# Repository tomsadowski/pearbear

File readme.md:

# Pearbear

2) Order the PCB
  * 1) Download the [specification file](mx/production/pearbear_mx.zip)
  * 2) Upload the file to a PCB [fabrication service](https://jlcpcb.com/)
3) Bill of Materials
  * a) 2x [Adafruit KB2040](https://www.adafruit.com/product/5302#tutorials)
    * product id: 5302
    * [datasheet](datasheets/Adafruit_KB2040_Pinout.pdf)
  * b) 2x [6P6C RJ11 socket](https://www.digikey.com/en/products/detail/w%C3%BCrth-elektronik/615006138421/2060609) 
    * manufacturer product number: 615006138421
    * digikey part number: 732-2113-ND
    * [datasheet](datasheets/WR-MJ.pdf)
  * c) 2x [6mm B3F-10xx tactile switches](https://www.digikey.com/en/products/detail/adafruit-industries-llc/367/10669771)
    * manufacturer product number: 367
    * digikey part number: 1528-367-ND
    * [datasheet](datasheets/B3F-1000-Omron.pdf)
  * d) 34x [Cherry MX switches](https://mechanicalkeyboards.com/products/cherry-mx2a-silent-red-45g-linear)
    * [datasheet](datasheets/Cherry_MX.pdf)
  * e) 34x [XDA Keycaps](https://ymdkey.com/products/xda-1u-new-keycapsblank-pbt-1-55mm)
  * f) Substrate
    * 1x Mousepad
    * gorilla glue
4) Assembly
  * 1) Solder 3.a - 3.d to PCB (beginners guide pending)
  * 2) Cut the mousepad into strips and glue the strips along the bottom of the PCB
5) Flash microcontrollers with qmk_firmware

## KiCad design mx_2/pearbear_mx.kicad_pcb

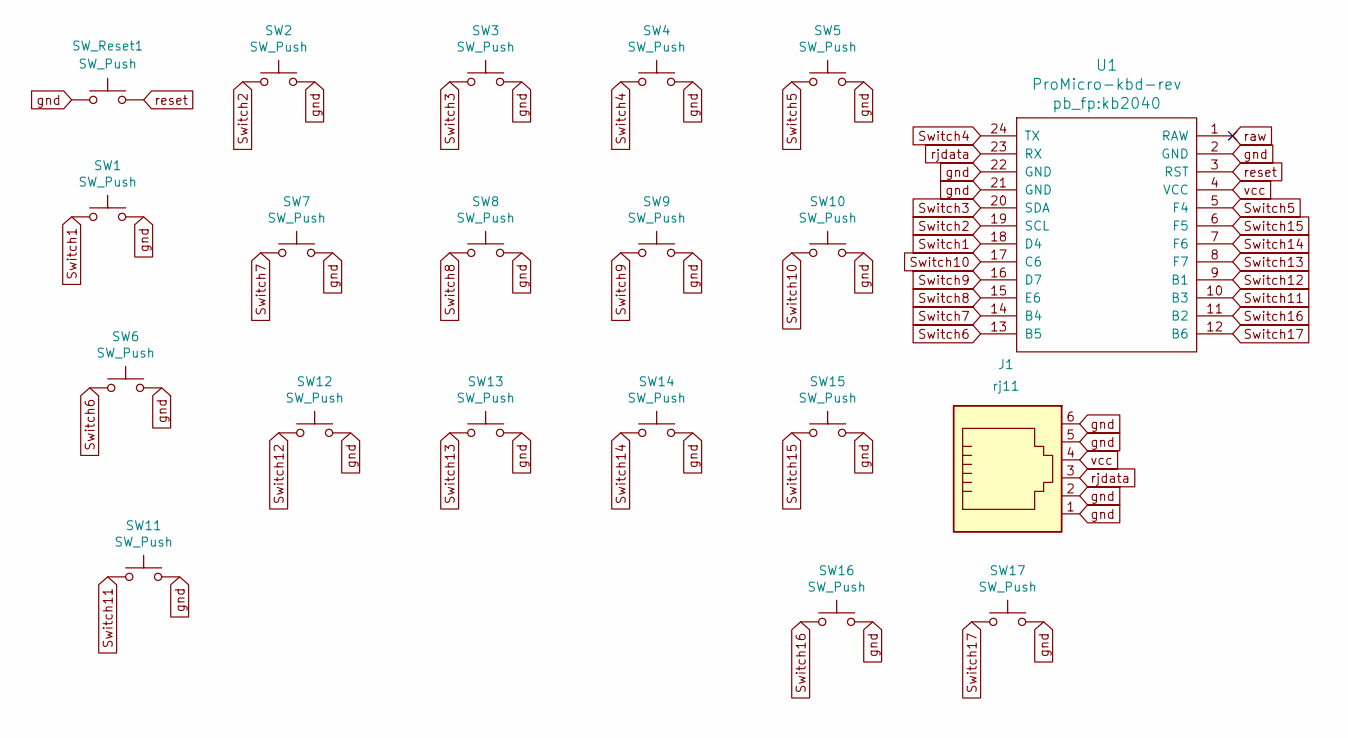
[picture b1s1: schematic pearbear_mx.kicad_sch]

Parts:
J1: rj11; RJ11_6P6C
SW1, SW2, SW3, SW4, SW5, SW6, SW7, SW8, SW9, SW10, SW11, SW12, SW13, SW14, SW15, SW16, SW17: SW_Push; SW_Cherry_MX
SW_Reset1: SW_Push; SW_TH_Tactile_Omron_B3F-10xx_reversible
U1: ProMicro-kbd-rev; kb2040

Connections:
Switch1: SW1.1, U1.18 (D4)
Switch2: SW2.1, U1.19 (SCL)
Switch3: SW3.1, U1.20 (SDA)
Switch4: SW4.1, U1.24 (TX)
Switch5: SW5.1, U1.5 (F4)
Switch6: SW6.1, U1.13 (B5)
Switch7: SW7.1, U1.14 (B4)
Switch8: SW8.1, U1.15 (E6)
Switch9: SW9.1, U1.16 (D7)
Switch10: SW10.1, U1.17 (C6)
Switch11: SW11.1, U1.10 (B3)
Switch12: SW12.1, U1.9 (B1)
Switch13: SW13.1, U1.8 (F7)
Switch14: SW14.1, U1.7 (F6)
Switch15: SW15.1, U1.6 (F5)
Switch16: SW16.1, U1.11 (B2)
Switch17: SW17.1, U1.12 (B6)
gnd: J1.1, J1.2, J1.5, J1.6, SW1.2, SW2.2, SW3.2, SW4.2, SW5.2, SW6.2, SW7.2, SW8.2, SW9.2, SW10.2, SW11.2, SW12.2, SW13.2, SW14.2, SW15.2, SW16.2, SW17.2, SW_Reset1.1, U1.2 (GND), U1.21 (GND), U1.22 (GND)
raw: U1.1 (RAW)
reset: SW_Reset1.2, U1.3 (RST)
rjdata: J1.3, U1.23 (RX)
vcc: J1.4, U1.4 (VCC)

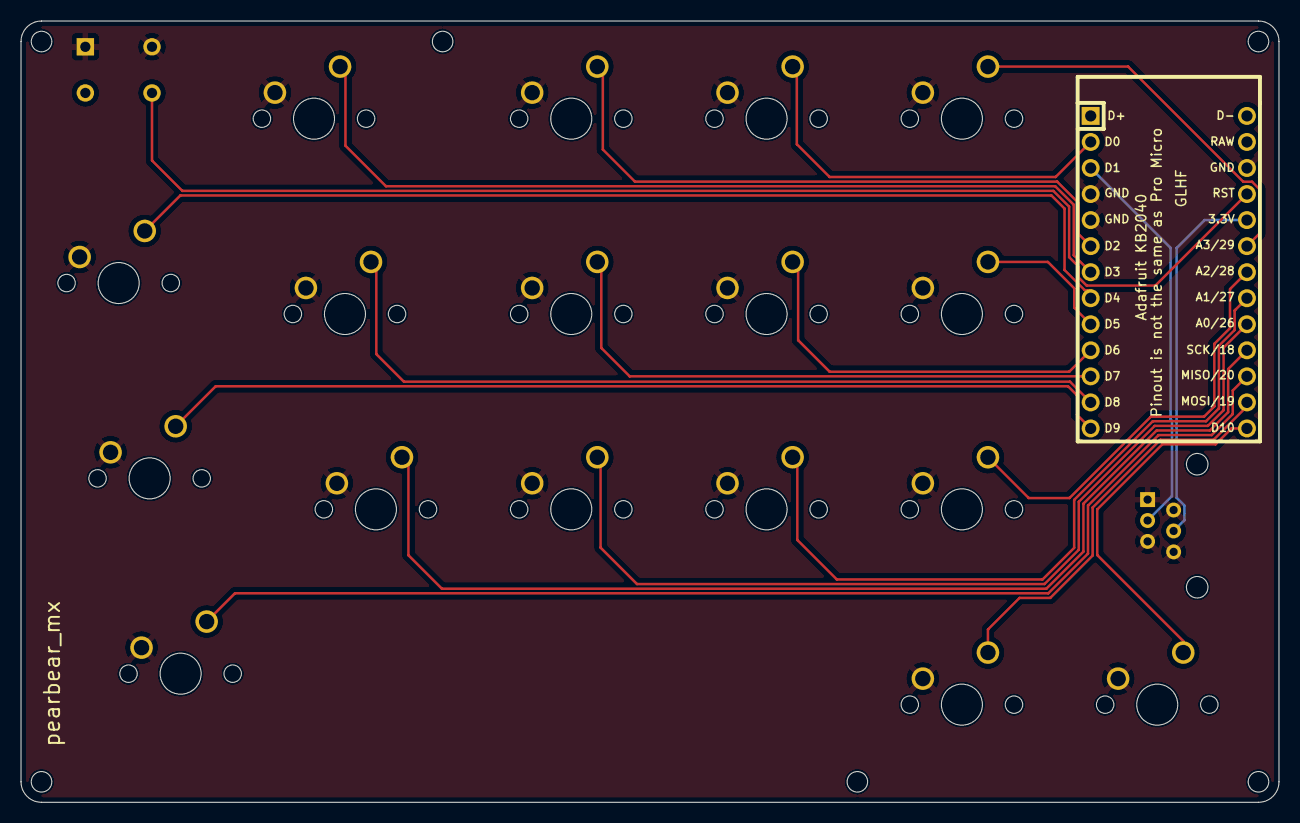
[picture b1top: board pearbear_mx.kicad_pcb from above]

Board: 2 copper layers, 122.7 x 76.2 mm, 20 parts (0 on the bottom side), 21 nets.

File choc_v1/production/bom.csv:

Designator,Footprint,Quantity,Value,LCSC Part #
J1,RJ11_6P6C_reversible,1,rj11,
"SW1, SW10, SW11, SW12, SW13, SW14, SW15, SW16, SW17, SW2, SW3, SW4, SW5, SW6, SW7, SW8, SW9",SW_Kailh_Choc_v1_reversible,17,SW_Push,
SW_RESET1,SW_TH_Tactile_Omron_B3F-10xx_reversible,1,SW_Push,
U1,ProMicro_reversible,1,ProMicro-kbd-rev,

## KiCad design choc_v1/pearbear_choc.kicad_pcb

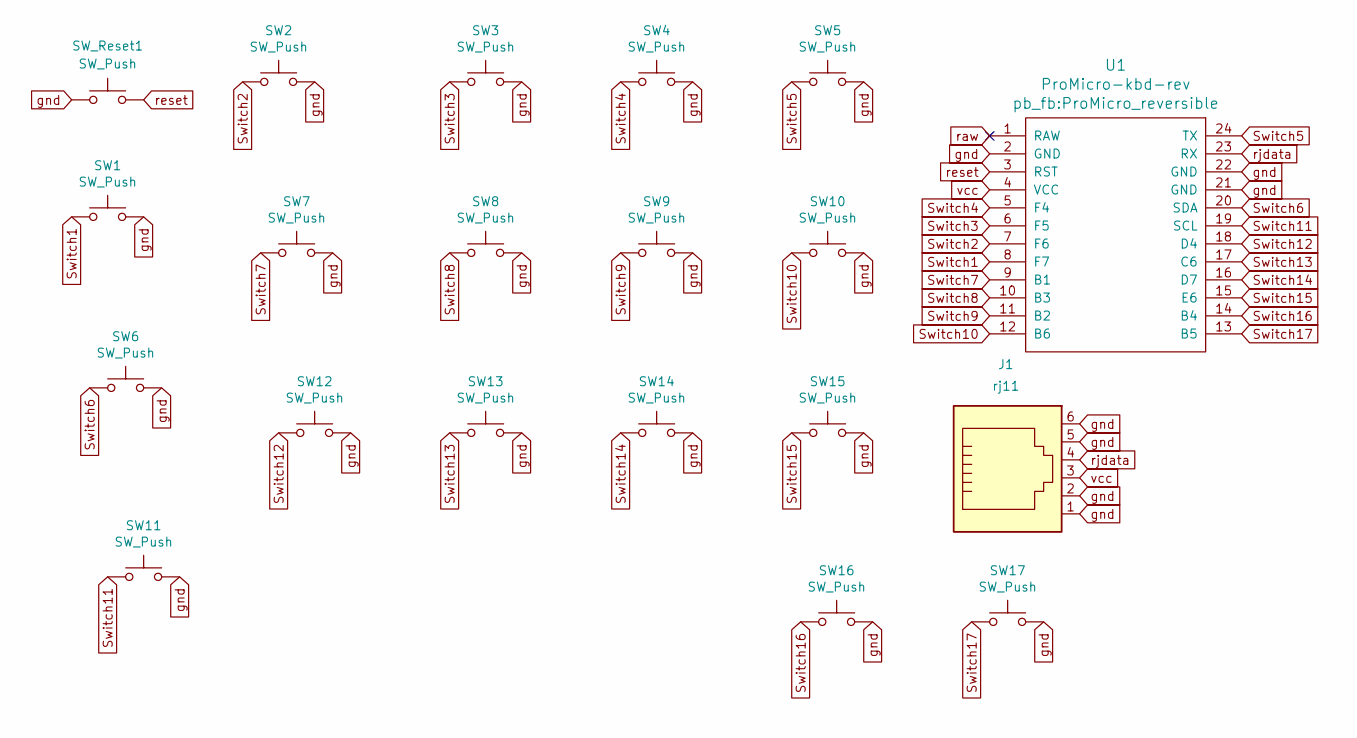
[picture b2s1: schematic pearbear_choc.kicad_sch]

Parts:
J1: rj11; RJ11_6P6C_reversible
SW1, SW2, SW3, SW4, SW5, SW6, SW7, SW8, SW9, SW10, SW11, SW12, SW13, SW14, SW15, SW16, SW17: SW_Push; SW_Kailh_Choc_v1_reversible
SW_Reset1: SW_Push; SW_TH_Tactile_Omron_B3F-10xx_reversible
U1: ProMicro-kbd-rev; ProMicro_reversible

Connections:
Switch1: SW1.1, U1.8 (F7)
Switch2: SW2.1, U1.7 (F6)
Switch3: SW3.1, U1.6 (F5)
Switch4: SW4.1, U1.5 (F4)
Switch5: SW5.1, U1.24 (TX)
Switch6: SW6.1, U1.20 (SDA)
Switch7: SW7.1, U1.9 (B1)
Switch8: SW8.1, U1.10 (B3)
Switch9: SW9.1, U1.11 (B2)
Switch10: SW10.1, U1.12 (B6)
Switch11: SW11.1, U1.19 (SCL)
Switch12: SW12.1, U1.18 (D4)
Switch13: SW13.1, U1.17 (C6)
Switch14: SW14.1, U1.16 (D7)
Switch15: SW15.1, U1.15 (E6)
Switch16: SW16.1, U1.14 (B4)
Switch17: SW17.1, U1.13 (B5)
gnd: J1.1, J1.2, J1.5, J1.6, SW1.2, SW2.2, SW3.2, SW4.2, SW5.2, SW6.2, SW7.2, SW8.2, SW9.2, SW10.2, SW11.2, SW12.2, SW13.2, SW14.2, SW15.2, SW16.2, SW17.2, SW_Reset1.1, U1.2 (GND), U1.21 (GND), U1.22 (GND)
raw: U1.1 (RAW)
raw_1: U1.1 (RAW)
raw_2: U1.1 (RAW)
raw_3: U1.1 (RAW)
raw_4: U1.1 (RAW)
reset: SW_Reset1.2, U1.3 (RST)
rjdata: J1.4, U1.23 (RX)
vcc: J1.3, U1.4 (VCC)

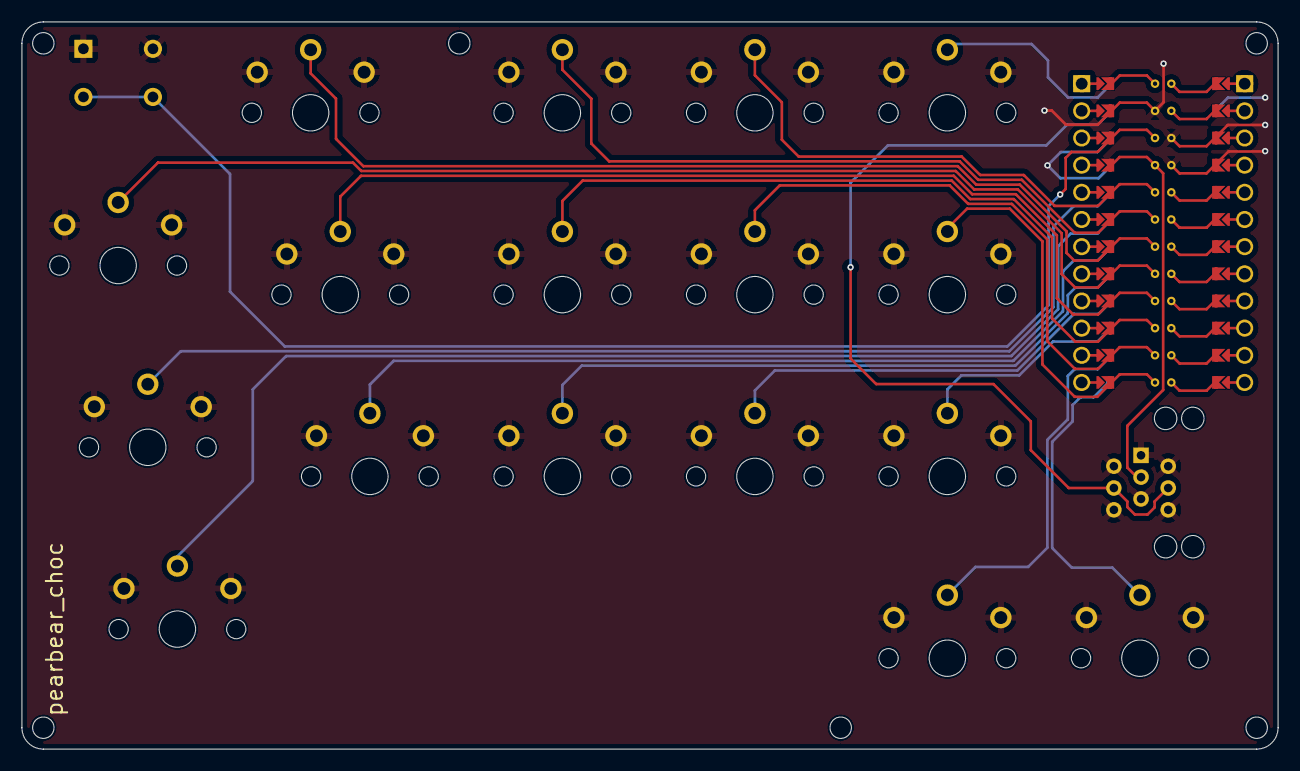
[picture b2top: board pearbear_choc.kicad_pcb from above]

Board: 2 copper layers, 117.5 x 68.0 mm, 20 parts (0 on the bottom side), 21 nets.

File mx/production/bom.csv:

Designator,Footprint,Quantity,Value,LCSC Part #
J1,RJ11_6P6C_reversible,1,rj11,
"SW1, SW10, SW11, SW12, SW13, SW14, SW15, SW16, SW17, SW2, SW3, SW4, SW5, SW6, SW7, SW8, SW9",SW_Cherry_MX_reversible,17,SW_Push,
SW_Reset1,SW_TH_Tactile_Omron_B3F-10xx_reversible,1,SW_Push,
U1,ProMicro_reversible,1,ProMicro-kbd-rev,

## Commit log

2024-10-22 we have air fryers why is everyone still fighting
2024-11-09 doc update
2025-02-15 choc
2025-05-09 more rj11 doc
2025-05-10 docs much
2025-05-10 docs much yes
2025-05-26 black
2025-06-05 first
2025-06-05 readmes
2025-06-09 shorter combo term
2025-07-31 inertia
2025-07-31 mouse
2025-07-31 good for quake
2025-08-05 good
2025-08-12 peeple
2025-08-14 2D game update for nine sols
2025-08-14 more 2d game update for nine sols
2025-09-03 newest
2025-09-03 newest 2
2025-09-03 newest 3
2025-09-03 pictures
2025-09-04 fix combo doc
2025-09-17 doc updates
2025-09-18 fix2
2025-09-18 fix3
2025-10-05 game layers are now transitional layers to more game layers
2025-11-05 readme updates
